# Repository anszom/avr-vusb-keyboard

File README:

A mostly-complete USB-based keyboard controller using atmega16 with V-USB.

Full description here: http://kuku.eu.org/?projects/keyboard/index

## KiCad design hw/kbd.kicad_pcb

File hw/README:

Project files for KiCad, made with kicad version 0.20131208+bzr4024.

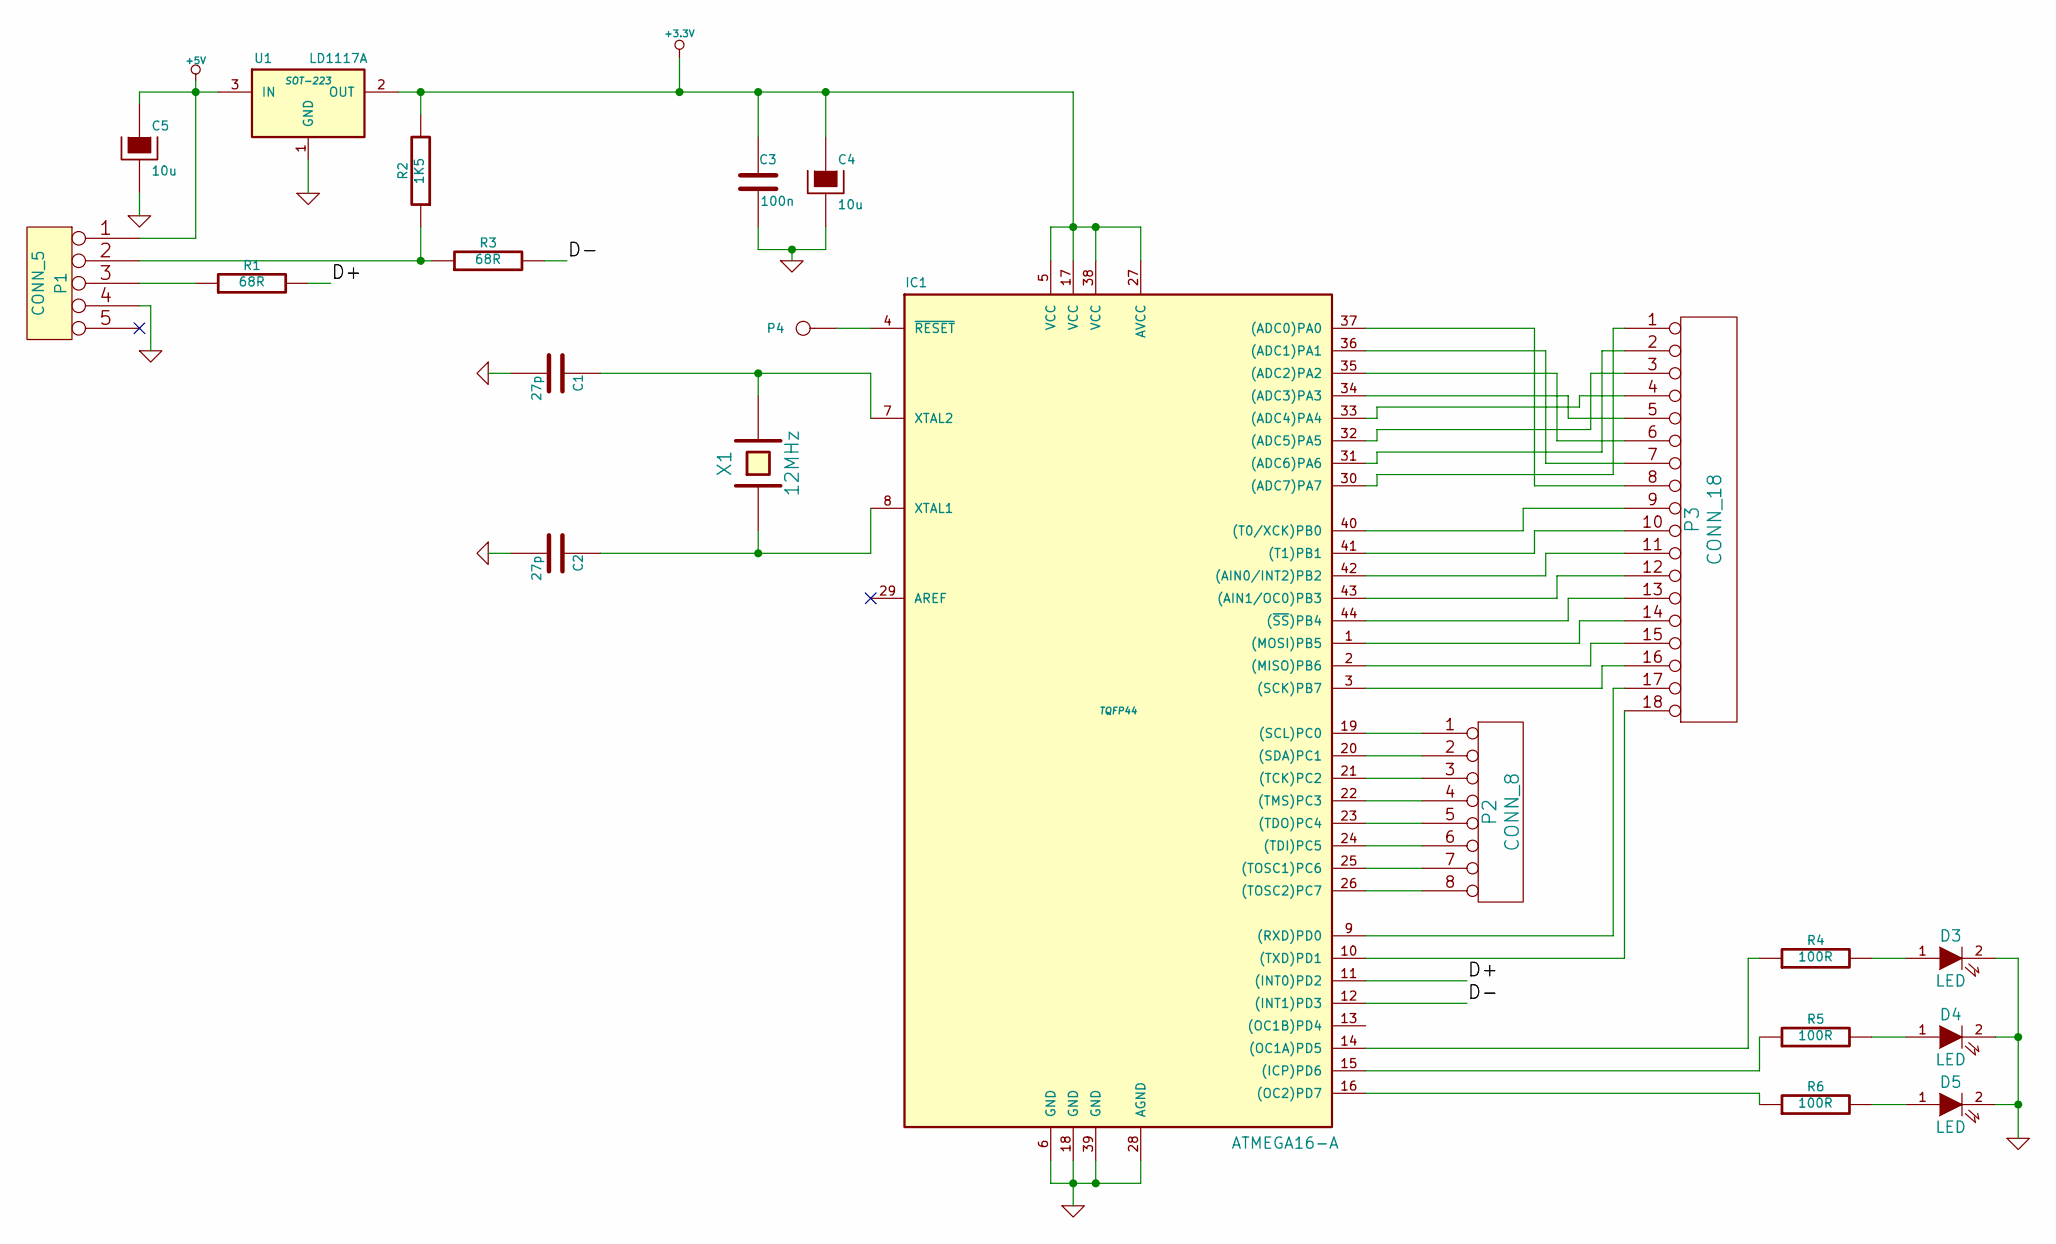
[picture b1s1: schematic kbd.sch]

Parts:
C1, C2: 27p
C3: 100n
C4, C5: 10u
D3, D4, D5: LED
IC1: ATMEGA16-A; TQFP44
P1: CONN_5
P2: CONN_8
P3: CONN_18
P4: CONN_1
R1, R3: 68R
R2: 1K5
R4, R5, R6: 100R
U1: LD1117A; SOT-223
X1: 12MHz

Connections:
+3.3V: C3.1, C4.1, IC1.5 (VCC), IC1.17 (VCC), IC1.27 (AVCC), IC1.38 (VCC), R2.2, U1.2 (OUT)
+5V: C5.1, P1.1, U1.3 (IN)
/D+: IC1.11 ((INT0)PD2), R1.2
/D-: IC1.12 ((INT1)PD3), R3.2
GND: C1.2, C2.2, C3.2, C4.2, C5.2, D3.2 (K), D4.2 (K), D5.2 (K), IC1.6 (GND), IC1.18 (GND), IC1.28 (AGND), IC1.39 (GND), P1.4, U1.1 (GND)
unnamed: IC1.9 ((RXD)PD0), P3.17
unnamed: IC1.44 ((~SS~)PB4), P3.13
unnamed: IC1.1 ((MOSI)PB5), P3.14
unnamed: IC1.2 ((MISO)PB6), P3.15
unnamed: IC1.3 ((SCK)PB7), P3.16
unnamed: IC1.10 ((TXD)PD1), P3.18
unnamed: IC1.4 (~RESET), P4.1
unnamed: IC1.41 ((T1)PB1), P3.10
unnamed: IC1.22 ((TMS)PC3), P2.4
unnamed: IC1.21 ((TCK)PC2), P2.3
unnamed: IC1.20 ((SDA)PC1), P2.2
unnamed: IC1.19 ((SCL)PC0), P2.1
unnamed: IC1.40 ((T0/XCK)PB0), P3.9
unnamed: IC1.42 ((AIN0/INT2)PB2), P3.11
unnamed: IC1.43 ((AIN1/OC0)PB3), P3.12
unnamed: D5.1 (A), R6.2
unnamed: D4.1 (A), R5.2
unnamed: D3.1 (A), R4.2
unnamed: IC1.23 ((TDO)PC4), P2.5
unnamed: P1.2, R2.1, R3.1
unnamed: P1.3, R1.1
unnamed: IC1.37 ((ADC0)PA0), P3.8
unnamed: IC1.36 ((ADC1)PA1), P3.7
unnamed: IC1.35 ((ADC2)PA2), P3.6
unnamed: IC1.30 ((ADC7)PA7), P3.1
unnamed: IC1.14 ((OC1A)PD5), R4.1
unnamed: IC1.15 ((ICP)PD6), R5.1
unnamed: IC1.16 ((OC2)PD7), R6.1
unnamed: IC1.26 ((TOSC2)PC7), P2.8
unnamed: IC1.25 ((TOSC1)PC6), P2.7
unnamed: IC1.24 ((TDI)PC5), P2.6
unnamed: IC1.32 ((ADC5)PA5), P3.3
unnamed: IC1.34 ((ADC3)PA3), P3.5
unnamed: IC1.33 ((ADC4)PA4), P3.4
unnamed: IC1.31 ((ADC6)PA6), P3.2
unnamed: C1.1, IC1.7 (XTAL2), X1.2
unnamed: C2.1, IC1.8 (XTAL1), X1.1

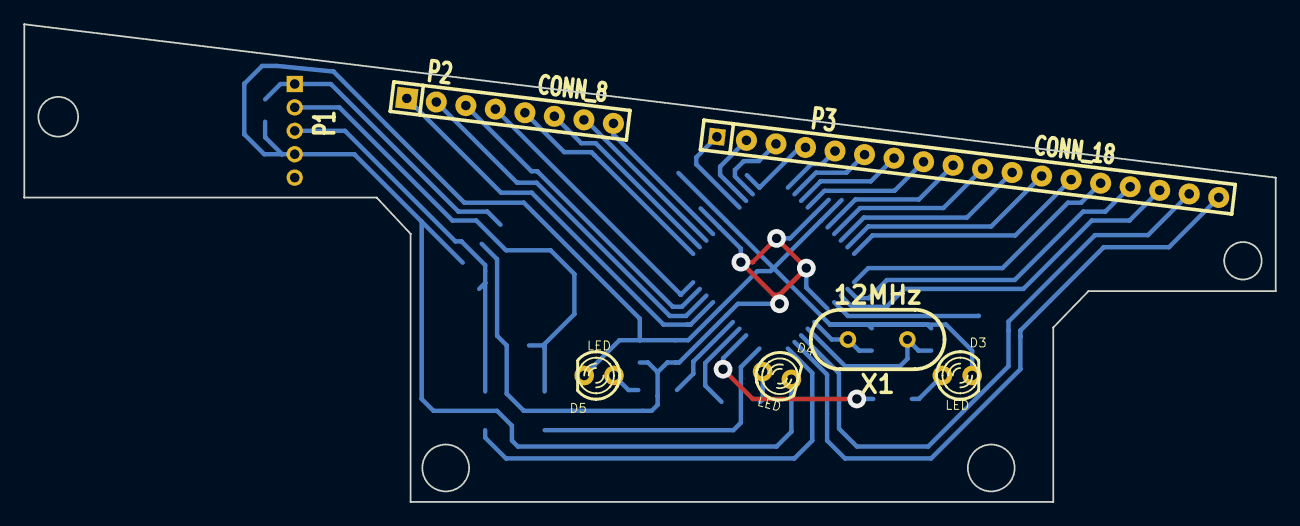
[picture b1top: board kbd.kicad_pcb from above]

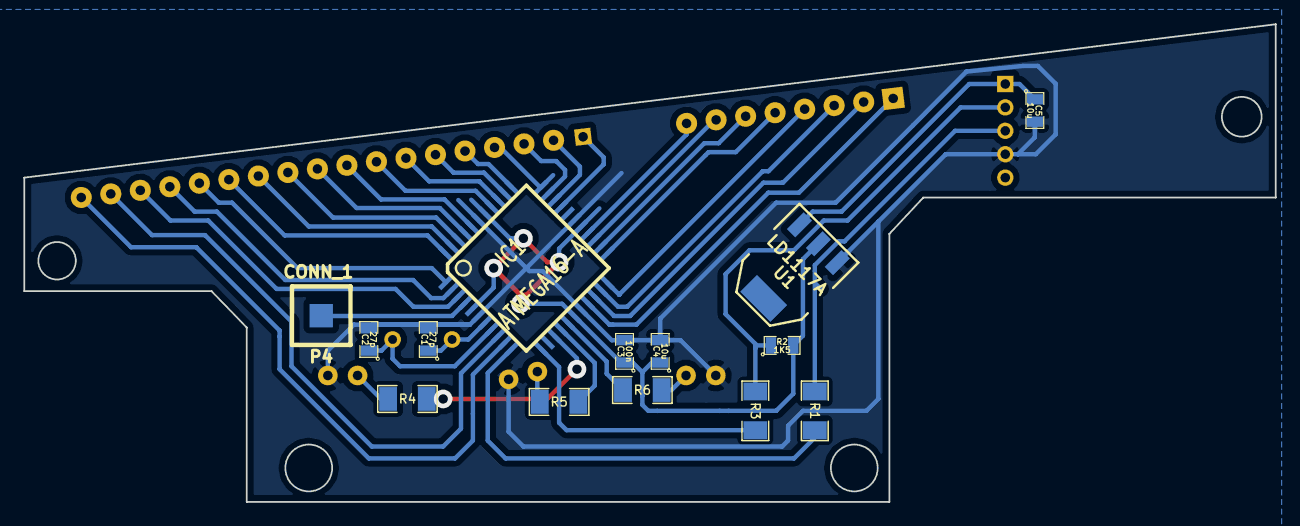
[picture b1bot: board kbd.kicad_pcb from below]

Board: 2 copper layers, 106.9 x 40.8 mm, 21 parts (14 on the bottom side), 42 nets.

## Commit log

2016-05-22 hardware: initial commit
2016-05-22 firmware: import vusb-20121206
2016-05-22 import avrusbboot.2006-06-25
    with minor adjustments to directory structure
2016-05-22 firmware: initial commit
2016-05-22 bootloader support
2016-05-22 Add USB wakeup support.
    1. Prepare custom USB configuration descriptor with USBATTR_REMOTEWAKE
    2. Use the USB_COUNT_SOF feature from VUSB. This requires:
    3. Change the VUSB's interrupt config from D+ to D- trigger
2016-05-22 Add README for avrusbboot host code
2016-05-22 Add GPL license to avrusbboot host code.
    With permission from the original author.
2016-05-22 Add main readme
